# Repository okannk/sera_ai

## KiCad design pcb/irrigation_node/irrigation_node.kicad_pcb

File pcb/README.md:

# Sera AI — PCB Design Files

KiCad 7.0 PCB projects for the Sera AI greenhouse automation system.
Three independent ESP32-S3 based nodes, each with W5500 SPI Ethernet.

---

## Node Overview

| Node | Directory | Board Size | Purpose |
|------|-----------|------------|---------|
| Sensor Node | `sensor_node/` | 100 × 80 mm | Multi-sensor acquisition (SHT40, SCD41, AS7341, TEROS-12) |
| Climate Node | `climate_node/` | 120 × 100 mm | 4-channel SSR actuator control (230V AC) |
| Irrigation Node | `irrigation_node/` | 120 × 100 mm | Atlas EZO probes + MOSFET valve drive (12V DC) |

---

## Directory Structure

```
pcb/
├── README.md
├── sensor_node/
│   ├── sensor_node.kicad_pro      KiCad 7.0 project file
│   ├── sensor_node.kicad_sch      Schematic (S-expression format)
│   ├── sensor_node.kicad_pcb      PCB layout
│   ├── bom.csv                    Bill of materials
│   ├── pick_and_place.csv         SMT assembly coordinates
│   └── gerber/
│       ├── sensor_node-F_Cu.gtl       Front copper
│       ├── sensor_node-B_Cu.gbl       Back copper (GND plane)
│       ├── sensor_node-F_Silkscreen.gto  Front silkscreen
│       ├── sensor_node-Edge_Cuts.gm1  Board outline
│       └── sensor_node.drl            Drill file (Excellon MM)
├── climate_node/
│   ├── climate_node.kicad_pro
│   ├── climate_node.kicad_sch
│   ├── climate_node.kicad_pcb
│   ├── bom.csv
│   ├── pick_and_place.csv
│   └── gerber/
│       ├── climate_node-F_Cu.gtl
│       ├── climate_node-B_Cu.gbl
│       ├── climate_node-F_Silkscreen.gto
│       ├── climate_node-Edge_Cuts.gm1
│       └── climate_node.drl
└── irrigation_node/
    ├── irrigation_node.kicad_pro
    ├── irrigation_node.kicad_sch
    ├── irrigation_node.kicad_pcb
    ├── bom.csv
    ├── pick_and_place.csv
    └── gerber/
        ├── irrigation_node-F_Cu.gtl
        ├── irrigation_node-B_Cu.gbl
        ├── irrigation_node-F_Silkscreen.gto
        ├── irrigation_node-Edge_Cuts.gm1
        └── irrigation_node.drl
```

---

## Node 1 — Sensor Node (100 × 80 mm)

### Purpose
Multi-parameter environmental sensing. Collects temperature, humidity, CO₂,
full-spectrum light, and soil moisture. Sends data via MQTT over Ethernet.

### Key Components

| Reference | Component | Description |
|-----------|-----------|-------------|
| U2 | ESP32-S3-DevKitC-1 | Main MCU, 2×22 header 2.54mm pitch |
| U3 | W5500 | Hardwired TCP/IP SPI Ethernet module |
| U1 | AMS1117-3.3 | SOT-223 LDO, 5V → 3.3V |
| PS1 | HLK-PM05 | AC-DC isolated, 220V → 5V 600mA |
| J1 | JST-XH 4p | SHT40 (T+H, I2C 0x44) |
| J2 | JST-XH 4p | SCD41 (CO₂, I2C 0x62) |
| J3 | JST-XH 4p | AS7341 (light spectrum, I2C 0x39) |
| J4 | JST-XH 3p | TEROS-12 (soil, SDI-12) |
| J7 | HR911105A | RJ45 with integrated magnetics |
| D4 | SMBJ5.0A | TVS diode, transient protection |
| D5 | BAT54 | Schottky, reverse polarity |
| C1-C2 | 100µF | Bulk electrolytic caps |
| C3-C10 | 10µF / 100nF | Decoupling capacitors |
| R1-R2 | 4.7kΩ | I2C pull-up resistors |
| R3-R5 | 330Ω | LED current limiting |
| D1-D3 | LED 0805 | Status: green (power), blue (net), red (alarm) |

### Pin Assignment (ESP32-S3)

| Signal | GPIO |
|--------|------|
| I2C SDA | GPIO8 |
| I2C SCL | GPIO9 |
| SPI MOSI | GPIO11 |
| SPI MISO | GPIO13 |
| SPI SCK | GPIO12 |
| SPI CS W5500 | GPIO10 |
| W5500 INT | GPIO14 |
| W5500 RST | GPIO15 |
| UART TX (debug) | GPIO43 |
| UART RX (debug) | GPIO44 |
| SDI-12 DATA | GPIO16 |
| nRESET | EN |

---

## Node 2 — Climate Node (120 × 100 mm)

### Purpose
4-channel solid-state relay (SSR) control for AC loads: irrigation pump,
heater, cooling unit, fan. PC817 optocouplers provide full galvanic isolation
between ESP32 3.3V logic and SSR control inputs.

### WARNING — HIGH VOLTAGE
This board carries **230V AC mains voltage**. The board is divided into:
- **Low-voltage zone** (top half, y < 60mm): ESP32, W5500, logic, LEDs — 3.3V/5V DC
- **High-voltage zone** (bottom half, y > 60mm): AC mains, MOV, fuse, SSR connectors

**Design requirements:**
- Minimum 6mm creepage/clearance between LV and HV
- Conformal coating mandatory on HV zone
- Use IEC 60950 / IEC 62368 compliant assembly practices
- Fuse: 10A fast-blow ceramic 5×20mm in inline holder

### Key Components

| Reference | Component | Description |
|-----------|-----------|-------------|
| U4-U7 | PC817 | DIP-4 optocoupler, CTR ≥ 100% |
| K1-K4 | G3MB-202P | Panel-mount SSR, 250VAC 2A |
| RV1 | S14K275 | MOV varistor 275V, L-N surge clamp |
| F1 | 10A 250V | Fast-blow ceramic fuse + holder |
| J_AC | Phoenix 5p | L / N / PE / LOAD1 / LOAD2 screw terminal |
| R1-R4 | 330Ω | PC817 input LED current limiters |

### SSR Channel Mapping

| Channel | GPIO | Load |
|---------|------|------|
| CH1 | GPIO38 | Irrigation pump |
| CH2 | GPIO39 | Heater |
| CH3 | GPIO40 | Cooling |
| CH4 | GPIO41 | Fan |

---

## Node 3 — Irrigation Node (120 × 100 mm)

### Purpose
Precision water quality monitoring with Atlas Scientific EZO probes, plus
direct 12V solenoid valve drive via logic-level N-MOSFET and flow measurement
with YF-S201 pulse-output flow sensor.

### Key Components

| Reference | Component | Description |
|-----------|-----------|-------------|
| U4 | LM2596S-12 | TO-263-5 buck converter, 5V→12V at 3A |
| L1 | 100µH | Axial inductor, LM2596 output filter |
| C11 | 220µF 25V | LM2596 output capacitor |
| Q1-Q2 | IRLZ44N | TO-220 logic-level N-MOSFET, 55V/47A |
| D6-D7 | 1N4007 | DO-41 flyback diodes for inductive loads |
| R9-R10 | 100Ω | MOSFET gate resistors |
| J1 | JST-XH 4p | Atlas EZO-pH (I2C 0x63) |
| J2 | JST-XH 4p | Atlas EZO-EC (I2C 0x64) |
| J3 | JST-XH 4p | Atlas EZO-DO (I2C 0x61) |
| J4 | JST-XH 4p | Atlas EZO-RTD (I2C 0x66) |
| J5 | JST-XH 4p | Atlas EZO-PMP (I2C 0x67) |
| J6-J7 | Phoenix 2p | Solenoid valve screw terminals |
| J8 | JST-XH 3p | YF-S201 flow sensor |
| R11 | 10kΩ | Flow sensor signal pull-up |
| C5-C9 | 100nF | Per-probe bypass capacitors |

### EZO Probe I2C Addresses

| Probe | I2C Address | Parameter |
|-------|-------------|-----------|
| EZO-pH | 0x63 | pH 0.001 precision |
| EZO-EC | 0x64 | Conductivity / TDS / salinity |
| EZO-DO | 0x61 | Dissolved oxygen |
| EZO-RTD | 0x66 | Temperature (RTD) |
| EZO-PMP | 0x67 | Peristaltic pump control |

### Valve Drive

- Valve supply: 12V from LM2596 buck (input 15-24V via DC jack or HLK-PM05 variant)
- IRLZ44N: Vgs_th = 1.0-2.0V, fully enhanced at 3.3V ESP32 output
- Gate resistor 100Ω limits dI/dt and parasitic oscillation
- 1N4007 flyback diodes protect MOSFET from inductive kick

---

## Common Design Notes

### Power Architecture (all nodes)
```
AC 220V ──► HLK-PM05 ──► +5V ──► AMS1117-3.3 ──► +3.3V (MCU, sensors)
                           │
                           └──► W5500 (5V tolerant)
                           │
                  (irr. node only)
                           └──► LM2596-12 ──► +12V (valves)
```

### SPI Ethernet (W5500) — all nodes
- Interface: SPI up to 80MHz (typically 20-40MHz in firmware)
- GPIO11 MOSI / GPIO13 MISO / GPIO12 SCK / GPIO10 CS
- GPIO14 INT (active-low interrupt)
- GPIO15 RST (active-low hardware reset)
- Full TCP/IP stack offloaded from ESP32

### PCB Stack-up (all nodes)
- 2-layer FR4, 1.6mm thickness
- F.Cu: signal + power routing
- B.Cu: GND plane (full pour)
- Soldermask: LPI green both sides
- Silkscreen: white, F side only
- Finish: HASL or ENIG

### Design Rules
| Rule | Value |
|------|-------|
| Min clearance (signal) | 0.2mm |
| Min clearance (power) | 0.3mm |
| Min clearance (HV AC) | 6.0mm |
| Min trace width (signal) | 0.25mm |
| Power traces | 1.0mm (5V/3.3V), 2.0mm (12V/AC) |
| Via drill | 0.6mm |
| Via diameter | 1.0mm |
| Min hole | 0.3mm |
| Board thickness | 1.6mm |
| Copper weight | 1oz (35µm) |

---

## Manufacturing

### Gerber Files (per node)
| File | Extension | Description |
|------|-----------|-------------|
| F_Cu | .gtl | Front copper layer |
| B_Cu | .gbl | Back copper layer |
| F_Silkscreen | .gto | Front silkscreen |
| Edge_Cuts | .gm1 | Board outline |
| Drill | .drl | Excellon drill file (mm) |

### Recommended PCB Manufacturers
- JLCPCB (jlcpcb.com) — standard 2-layer, excellent price
- PCBWay (pcbway.com) — good for prototypes
- OSH Park (oshpark.com) — US-based, purple boards

### Assembly Notes
- All SMD components on F.Cu only (single-side SMT)
- THT components: ESP32 headers, connectors, caps, MOSFETs
- Hand-solder or selective soldering for THT after SMT reflow
- Apply conformal coating (Climate Node HV zone is mandatory)

---

## Revision History

| Rev | Date | Author | Notes |
|-----|------|--------|-------|
| 1.0 | 2026-03-11 | Sera AI | Initial release — all 3 nodes |

---

*Generated for Sera AI Greenhouse Automation System — KiCad 7.0*

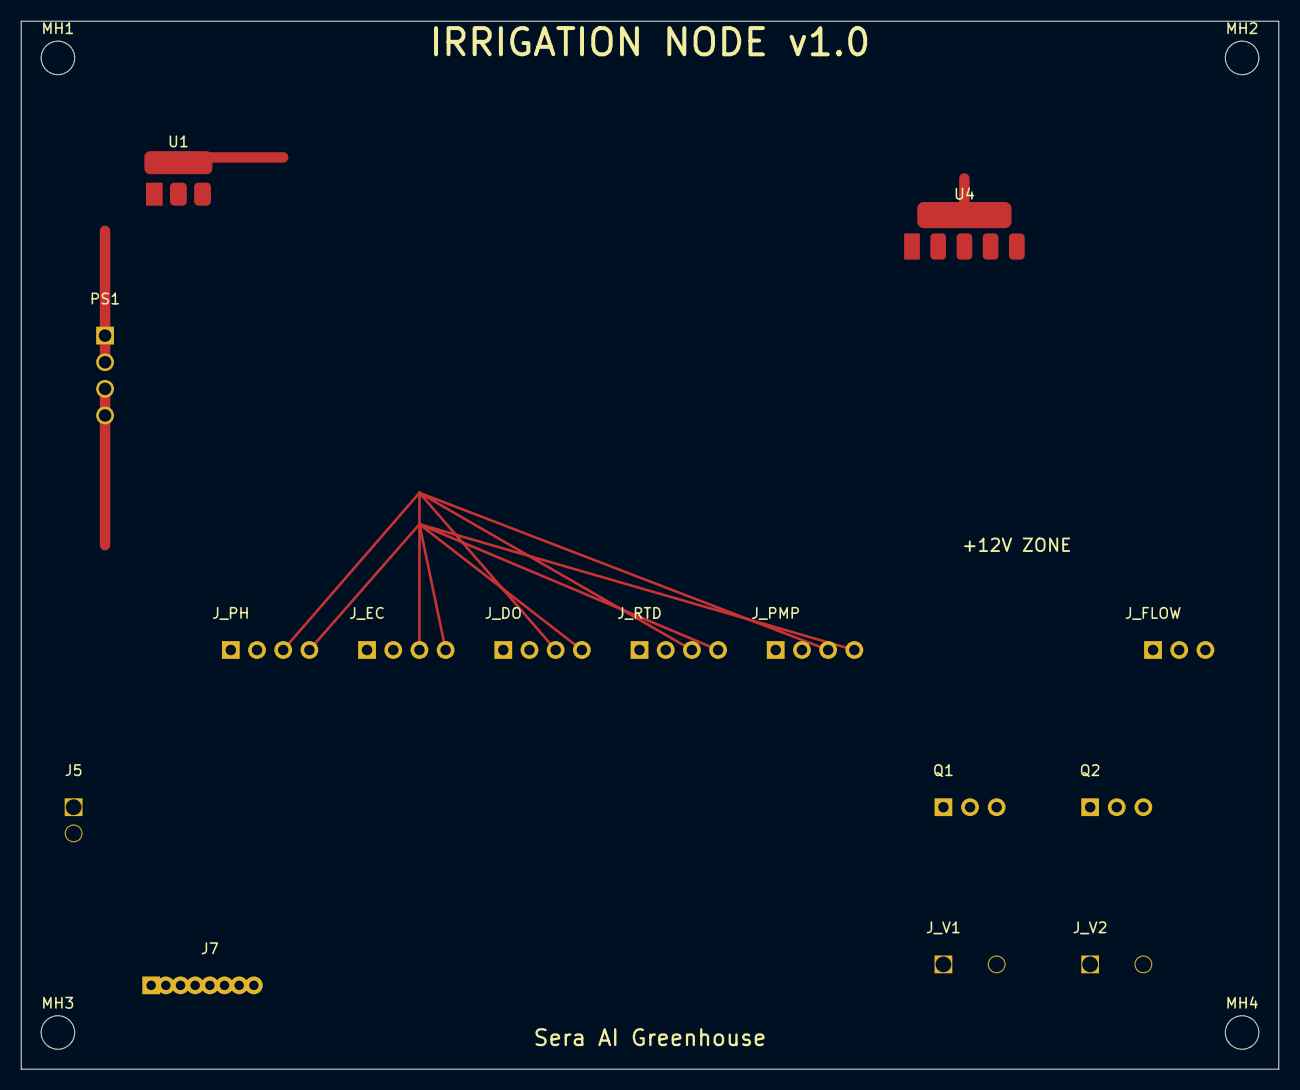
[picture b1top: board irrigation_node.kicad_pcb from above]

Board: 2 copper layers, 120.0 x 100.0 mm, 19 parts (0 on the bottom side), 8 nets.

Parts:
J5: DC_Jack; BarrelJack_Kycon_KLDX-0202-A_Horizontal
J7: HR911105A; RJ45_Amphenol_RJHSE538X_Horizontal
J_DO: EZO_3; JST_XH_B4B-XH-A_1x04_P2.50mm_Vertical
J_EC: EZO_2; JST_XH_B4B-XH-A_1x04_P2.50mm_Vertical
J_FLOW: YF-S201; JST_XH_B3B-XH-A_1x03_P2.50mm_Vertical
J_PH: EZO_1; JST_XH_B4B-XH-A_1x04_P2.50mm_Vertical
J_PMP: EZO_5; JST_XH_B4B-XH-A_1x04_P2.50mm_Vertical
J_RTD: EZO_4; JST_XH_B4B-XH-A_1x04_P2.50mm_Vertical
J_V1: VALVE_1; TerminalBlock_bornier-2_P5.08mm
J_V2: VALVE_2; TerminalBlock_bornier-2_P5.08mm
MH1, MH2, MH3, MH4: MountingHole_3.2mm_M3
PS1: HLK-PM05; PinHeader_1x04_P2.54mm_Vertical
Q1: IRLZ44N_V1; TO-220-3_Vertical
Q2: IRLZ44N_V2; TO-220-3_Vertical
U1: AMS1117-3.3; SOT-223-3_TabPin2
U4: LM2596-12V; TO-263-5_TabPin3

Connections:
+3V3: J_DO.2, J_EC.2, J_PH.2, J_PMP.2, J_RTD.2, U1.2, U1.4
+5V: J5.1, J_FLOW.1, PS1.3, U1.3, U4.1
+12V: J_V1.2, J_V2.2, Q1.3, Q2.3, U4.3, U4.tab
GND: J5.2, J_DO.1, J_EC.1, J_FLOW.3, J_PH.1, J_PMP.1, J_RTD.1, PS1.4, U1.1, U4.4
I2C_SCL: J_DO.4, J_EC.4, J_PH.4, J_PMP.4, J_RTD.4
I2C_SDA: J_DO.3, J_EC.3, J_PH.3, J_PMP.3, J_RTD.3
VALVE1: J_V1.1, Q1.2
VALVE2: J_V2.1, Q2.2

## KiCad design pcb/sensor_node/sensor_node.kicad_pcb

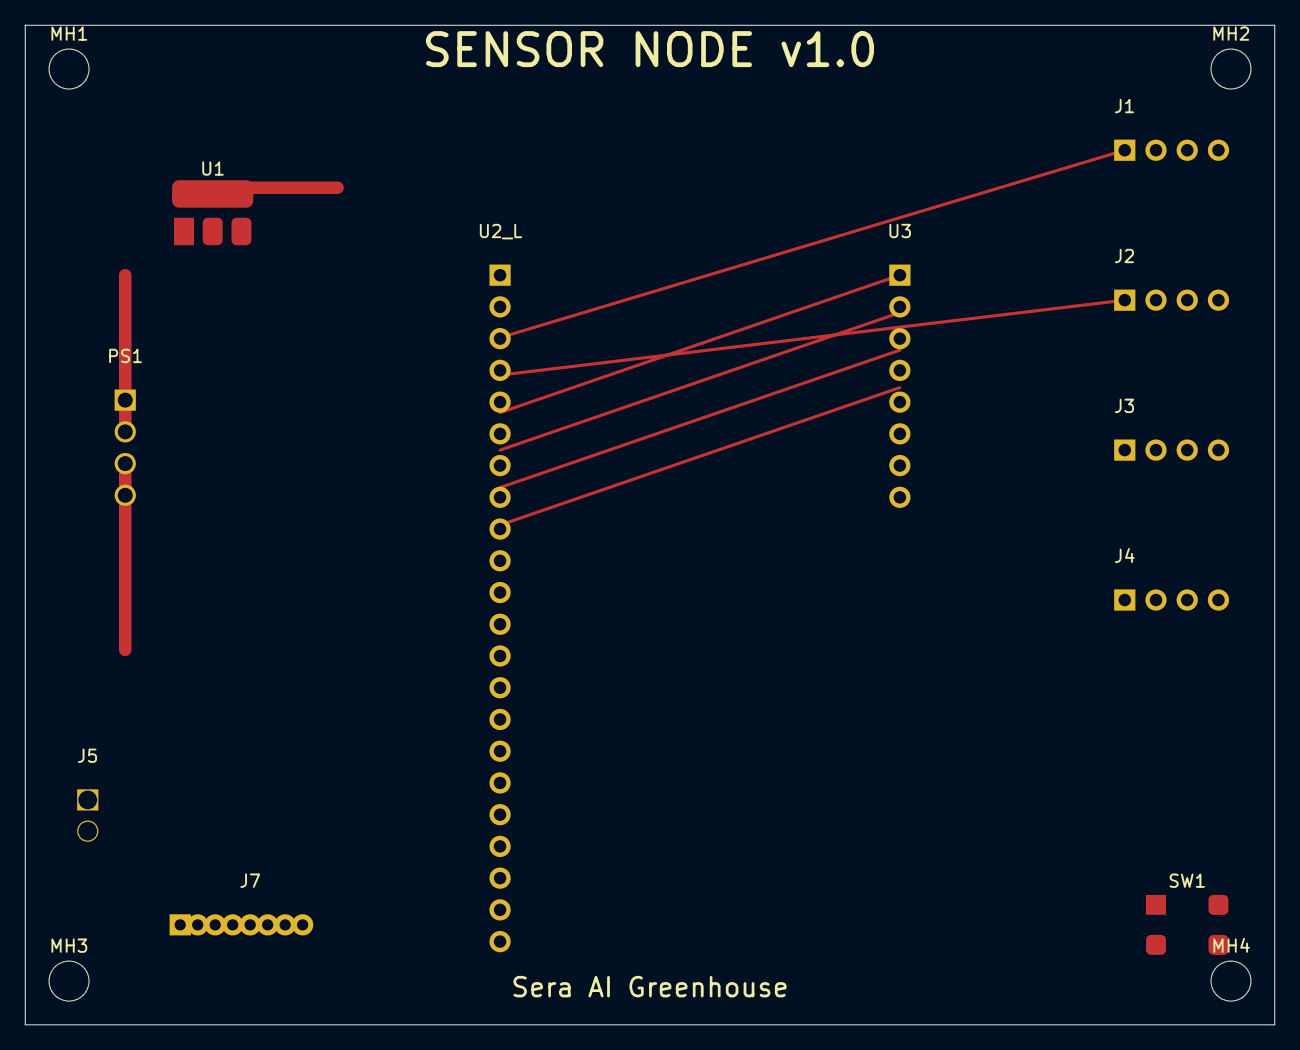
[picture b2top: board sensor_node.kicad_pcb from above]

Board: 2 copper layers, 100.0 x 80.0 mm, 15 parts (0 on the bottom side), 5 nets.

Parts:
J1: SHT40; JST_XH_B4B-XH-A_1x04_P2.50mm_Vertical
J2: SCD41; JST_XH_B4B-XH-A_1x04_P2.50mm_Vertical
J3: AS7341; JST_XH_B4B-XH-A_1x04_P2.50mm_Vertical
J4: TEROS12; JST_XH_B4B-XH-A_1x04_P2.50mm_Vertical
J5: DC_Jack; BarrelJack_Kycon_KLDX-0202-A_Horizontal
J7: HR911105A; RJ45_Amphenol_RJHSE538X_Horizontal
MH1, MH2, MH3, MH4: MountingHole_3.2mm_M3
PS1: HLK-PM05; PinHeader_1x04_P2.54mm_Vertical
SW1: RESET; SW_SPST_SKQG_WithStem
U1: AMS1117-3.3; SOT-223-3_TabPin2
U2_L: ESP32-S3-Left; PinHeader_1x22_P2.54mm_Vertical
U3: W5500-EVB; PinHeader_1x08_P2.54mm_Vertical

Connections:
+3V3: J1.2, J2.2, J3.2, J4.2, U1.2, U1.4, U2_L.21
+5V: J5.1, PS1.3, U1.3, U2_L.22, U3.3
GND: J1.1, J2.1, J3.1, J4.1, J5.2, PS1.4, U1.1, U2_L.20, U3.2
I2C_SCL: J1.4, J2.4, J3.4, J4.4
I2C_SDA: J1.3, J2.3, J3.3, J4.3

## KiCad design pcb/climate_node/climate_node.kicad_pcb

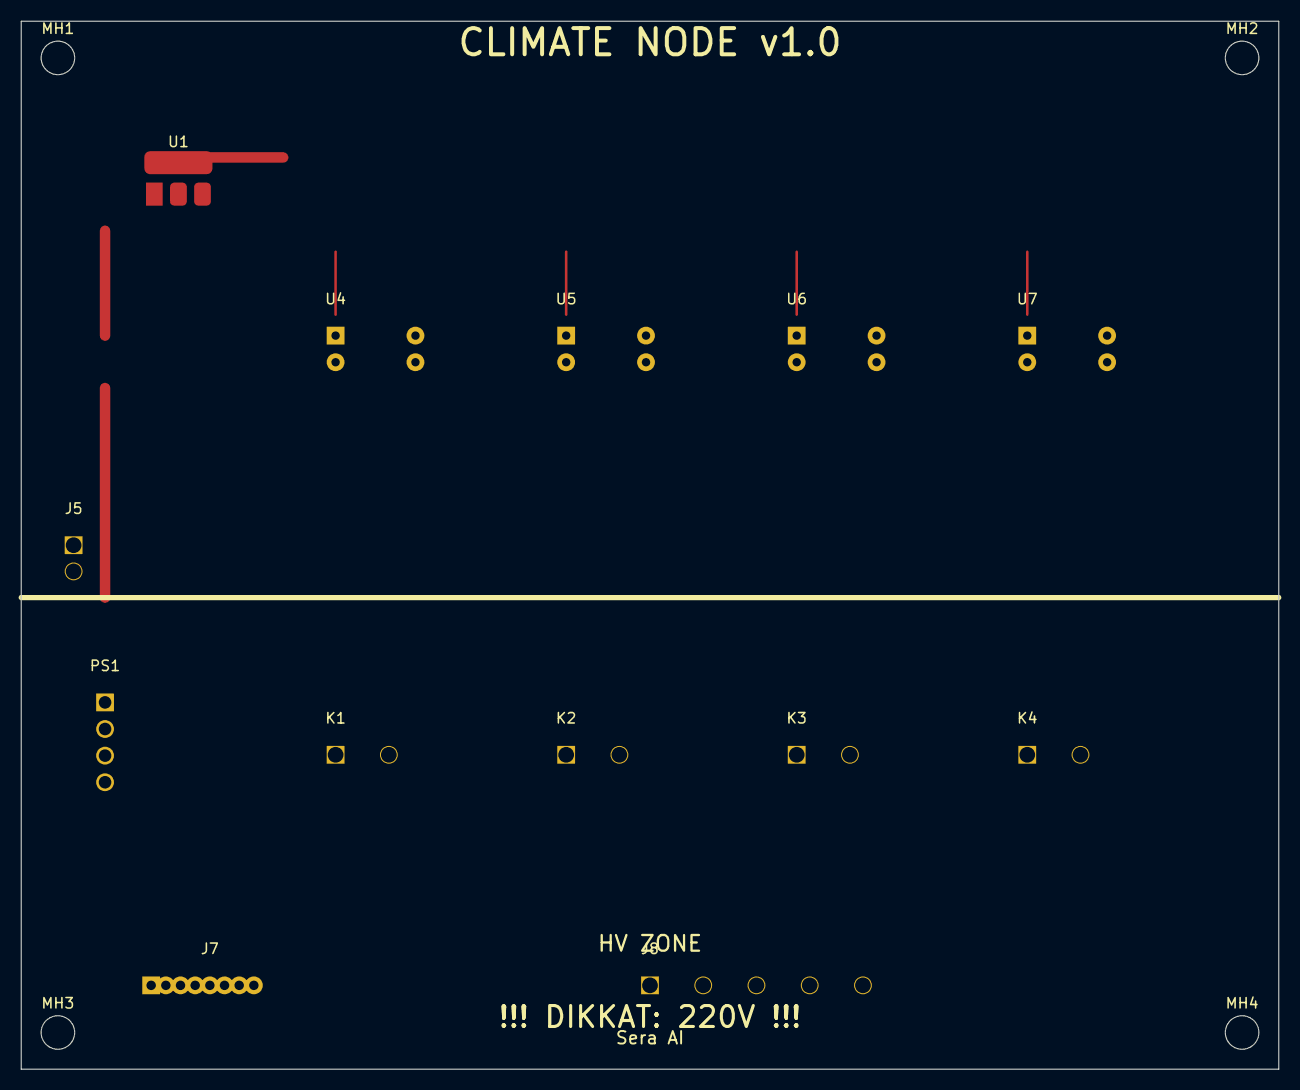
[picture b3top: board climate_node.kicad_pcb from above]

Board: 2 copper layers, 120.0 x 100.0 mm, 17 parts (0 on the bottom side), 3 nets.

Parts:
J5: DC_Jack; BarrelJack_Kycon_KLDX-0202-A_Horizontal
J7: HR911105A; RJ45_Amphenol_RJHSE538X_Horizontal
J8: AC_TERM; TerminalBlock_Phoenix_MKDS-1,5-5_1x05
K1: SSR_LOAD1; TerminalBlock_bornier-2_P5.08mm
K2: SSR_LOAD2; TerminalBlock_bornier-2_P5.08mm
K3: SSR_LOAD3; TerminalBlock_bornier-2_P5.08mm
K4: SSR_LOAD4; TerminalBlock_bornier-2_P5.08mm
MH1, MH2, MH3, MH4: MountingHole_3.2mm_M3
PS1: HLK-PM05; PinHeader_1x04_P2.54mm_Vertical
U1: AMS1117-3.3; SOT-223-3_TabPin2
U4: PC817_SSR1; DIP-4_W7.62mm
U5: PC817_SSR2; DIP-4_W7.62mm
U6: PC817_SSR3; DIP-4_W7.62mm
U7: PC817_SSR4; DIP-4_W7.62mm

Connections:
+3V3: U1.2, U1.4
+5V: J5.1, PS1.3, U1.3
GND: J5.2, PS1.4, U1.1

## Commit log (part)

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2026-03-16 feat: dashboard eklendi
